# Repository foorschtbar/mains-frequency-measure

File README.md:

# mains frequency measurement unit
for the RaspebrryPi or USB(TTL)Converter.

Simple electronics as a basis for measuring the mains frequency of power networks.
Use in industry, science, education or hobby.

## EN
Mains frequency measurement Base board for the RaspberryPi and USB-TTL converter

The circuit board presented here enables the exact mains frequency measurement of the power supply system (50 Hz and 60Hz). It is universally constructed and can be operated with a RaspberryPi 3/4 as well as with a USB-TTL converter.
The output of the measurement data is done via the serial interface of the used ATMega328. The µC software is programmed with the Arduino IDE. The program can be easily extended or adapted. 
The reproduction is very simple.

## DE
Netzfrequenz-Messung Basisplatine für den RaspberryPi und USB-TTL-Konverter

Die hier vorgestelle Platine ermöglicht die genaue Netzfrequenzmessung des Stromnetzes (50 Hz und 60Hz). Sie ist universell aufgebaut und kann sowohl mit einem RaspberryPi 3/4 als auch mit einem USB-TTL-Konverter betrieben werden.
Die Ausgabe der Messdaten erfolgt über die serielle Schnittstelle des verwendetet ATMega328. Die µCSoftware ist programmiert mit der Arduino-IDE. Das Programm lässt sich problemlos erweitern oder anpassen. 
Der Nachbau ist sehr einfach.

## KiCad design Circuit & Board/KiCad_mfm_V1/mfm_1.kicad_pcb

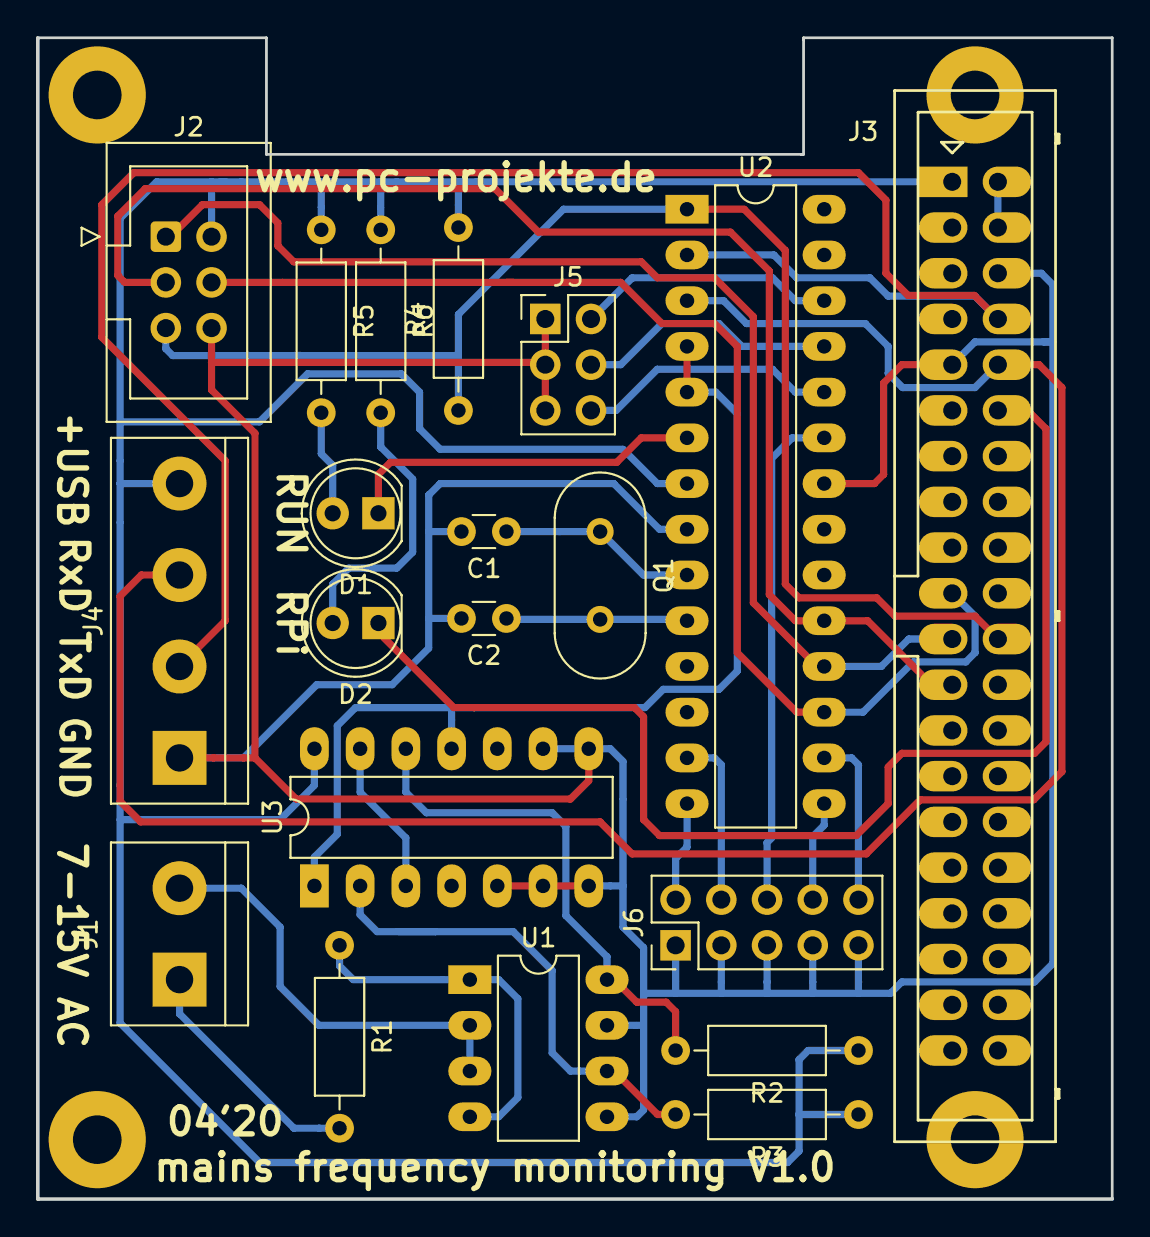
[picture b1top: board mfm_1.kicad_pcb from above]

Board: 2 copper layers, 59.7 x 64.5 mm, 20 parts (0 on the bottom side), 30 nets.

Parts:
C1, C2: 39pF; C_Disc_D3.0mm_W1.6mm_P2.50mm
D1, D2: LED; LED_D5.0mm_Clear
J1: Conn_01x02_Female; TerminalBlock_bornier-2_P5.08mm
J2: Conn_02x03_Odd_Even; IDC-Header_2x03_P2.54mm_Vertical
J3: Raspberry_Pi_2_3; Multicomp_MC9A12-4034_2x20x2.54mm_Straight
J4: Conn_01x04_Female; TerminalBlock_bornier-4_P5.08mm
J5: Conn_02x03_Odd_Even; PinHeader_2x03_P2.54mm_Vertical
J6: Conn_02x05_Odd_Even; PinHeader_2x05_P2.54mm_Vertical
Q1: 10MHz; Crystal_HC49-4H_Vertical
R1, R2, R3: 1k; R_Axial_DIN0207_L6.3mm_D2.5mm_P10.16mm_Horizontal
R4: 1K; R_Axial_DIN0207_L6.3mm_D2.5mm_P10.16mm_Horizontal
R5, R6: 100; R_Axial_DIN0207_L6.3mm_D2.5mm_P10.16mm_Horizontal
U1: PC827; DIP-8_W7.62mm_LongPads
U2: ATmega328-PU; DIP-28_W7.62mm_LongPads
U3: 4093; DIP-14_W7.62mm_LongPads

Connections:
+3V3: J2.2, J3.1, J4.4, R2.1, R3.1, R4.2, R5.1, R6.1, U2.7, U3.14
+5V: J3.2, J3.4
CLK: J2.3, J3.23, U2.19
GND: C1.2, C2.2, J2.6, J3.6, J3.9, J4.1, J5.1, J5.3, J5.5, J6.1, J6.3, J6.5, J6.7, J6.9, U1.5, U1.7, U2.8, U2.22, U3.5, U3.6, U3.7, U3.8, U3.9
LED1: D1.1, U2.6
LED2: D2.1, J3.12
MISO: J2.1, J3.21, U2.18
MOSI: J2.4, J3.19, U2.17
unnamed: C1.1, Q1.1, U2.9
unnamed: C2.1, Q1.2, U2.10
unnamed: D1.2, R5.2
unnamed: D2.2, R6.2
unnamed: J1.1, R1.2
unnamed: J1.2, U1.2, U1.3
unnamed: R1.1, U1.1, U1.4
unnamed: R2.2, U1.8, U3.12
unnamed: R3.2, U1.6, U3.2
unnamed: U2.4, U2.5, U3.1, U3.11
unnamed: U3.3, U3.13
Pin13: J6.4, U2.13
Pin14: J6.2, U2.14
Pin15: J6.8, U2.15
Pin16: J6.10, U2.16
Pin23: J6.6, U2.23
Pin24: J5.6, U2.24
Pin25: J5.4, U2.25
Pin26: J5.2, U2.26
RST: J2.5, J3.22, R4.1, U2.1
RxD: J3.8, J4.2, U2.2
TxD: J3.10, J4.3, U2.3

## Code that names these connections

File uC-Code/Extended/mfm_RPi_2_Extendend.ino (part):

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bool DeltaB = false;                                //  Hilfsvariable Delta B-Messung erkannt

//Binäreingänge Protokolleinstellungen
const byte Jumper51 =  A3;                  // Pin26 A3
const byte Jumper52 =  A2;                  // Pin25 A2
const byte Jumper53 =  A1;                  // Pin24 A1
byte Protokoll;

// Binärausgaben
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
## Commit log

2020-03-30 Add new directory
2020-03-30 Add new file
2020-03-30 Update license
2020-03-30 Update Hardware licence
2020-05-04 Deleted RPi Code/Base Code/.gitkeep, RPi Code/.gitkeep files
2020-05-04 Update µC-Code/Base Code/.gitkeep, µC-Code/Extended/.gitkeep, µC-Code/.gitkeep files
2020-05-04 Upload µC File (Arduino)
2020-05-04 Upload New File
2020-05-04 Deleted README.md
2020-05-04 Update Circuit &amp; Board/KiCad_mfm_V1/.gitkeep, Circuit &amp; Board/KiCad_mfm_V1/mfm_1-cache.lib, Circuit &amp; Board/KiCad_mfm_V1/mfm_1-rescue.lib, Circuit &amp; Board/KiCad_mfm_V1/mfm_1.kicad_pcb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
2020-05-25 Deleted Documentation/RPi_Netzfrequenzmessung_Basis_Gesamtbeschreibung.pdf
2020-05-25 Deleted Documentation/RPi_Mains_Frequency_Measurement_Basic_Description.pdf
2020-05-30 Deleted Documentation/RPi_mains_frequency_measurement_Basis_description.pdf
2021-02-09 Upload first extended version
2021-02-09 Upload first extrended version
2021-02-09 Upload first version extenden HEX-File
2021-10-04 Deleted uC-Code/Base Code/mfm_RPi_1.ino.standard.hex
2022-05-03 Migrated to KiCAD v6 and updated footprints

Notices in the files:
uC-Code/Extended/mfm_RPi_2_Extendend.ino:
Software unter GNU GPL3-Lizenz
